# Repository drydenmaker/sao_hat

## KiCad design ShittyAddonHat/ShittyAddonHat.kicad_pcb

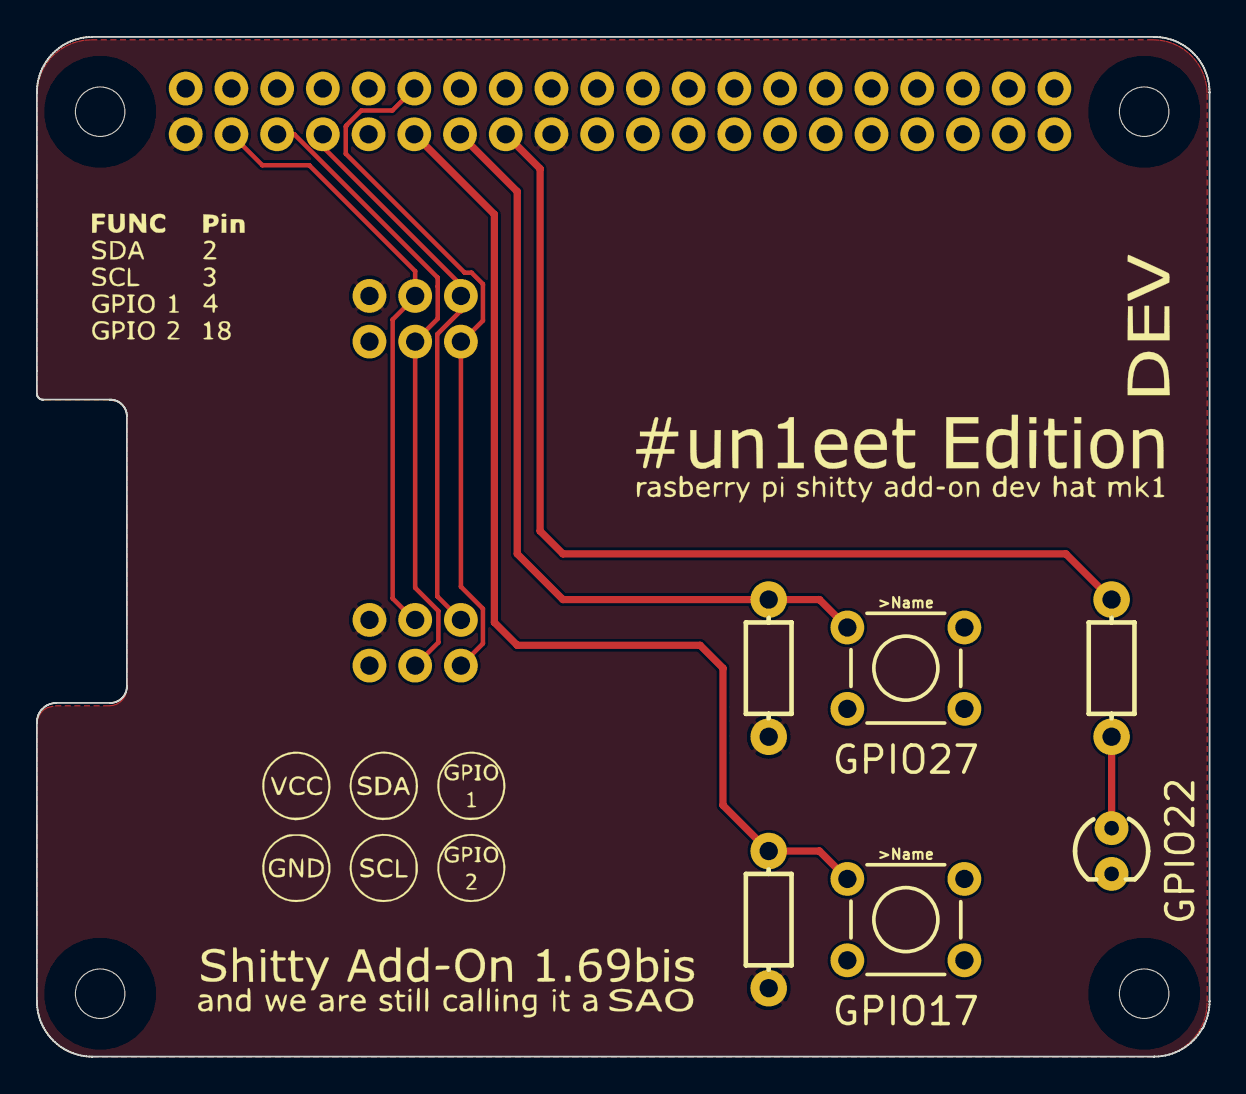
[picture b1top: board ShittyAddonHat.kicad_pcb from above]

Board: 2 copper layers, 65.1 x 56.7 mm, 9 parts (0 on the bottom side), 11 nets.

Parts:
D1: LED_3MM
J1, J2: 2X3-NS
PI_GPIO: 2X20_NOSILK
R1, R2: 10k; AXIAL-0.3-KIT
R3: 22; AXIAL-0.3-KIT
S1, S2: TACTILE_SWITCH_PTH_6.0MM

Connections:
5V: PI_GPIO.2, PI_GPIO.4
GND: D1.K, J1.1, J2.1, PI_GPIO.6, PI_GPIO.9, PI_GPIO.14, PI_GPIO.20, PI_GPIO.25, PI_GPIO.30, PI_GPIO.34, PI_GPIO.39, S1.3, S2.3
GPIO4: J1.6, J2.6, PI_GPIO.7
GPIO17: PI_GPIO.11, R1.P$2, S1.1
GPIO18: J1.5, J2.5, PI_GPIO.12
GPIO22: PI_GPIO.15, R3.P$1
GPIO27: PI_GPIO.13, R2.P$2, S2.1
unnamed: D1.A, R3.P$2
SCL: J1.3, J2.3, PI_GPIO.5
SDA: J1.4, J2.4, PI_GPIO.3
VCC: J1.2, J2.2, PI_GPIO.1, PI_GPIO.17, R1.P$1, R2.P$1

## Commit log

2019-04-22 just before silk change
2019-05-19 mk2 run 1 changes, furshur
2019-05-27 adding output from Inkscape
2019-05-27 updating gitignore
